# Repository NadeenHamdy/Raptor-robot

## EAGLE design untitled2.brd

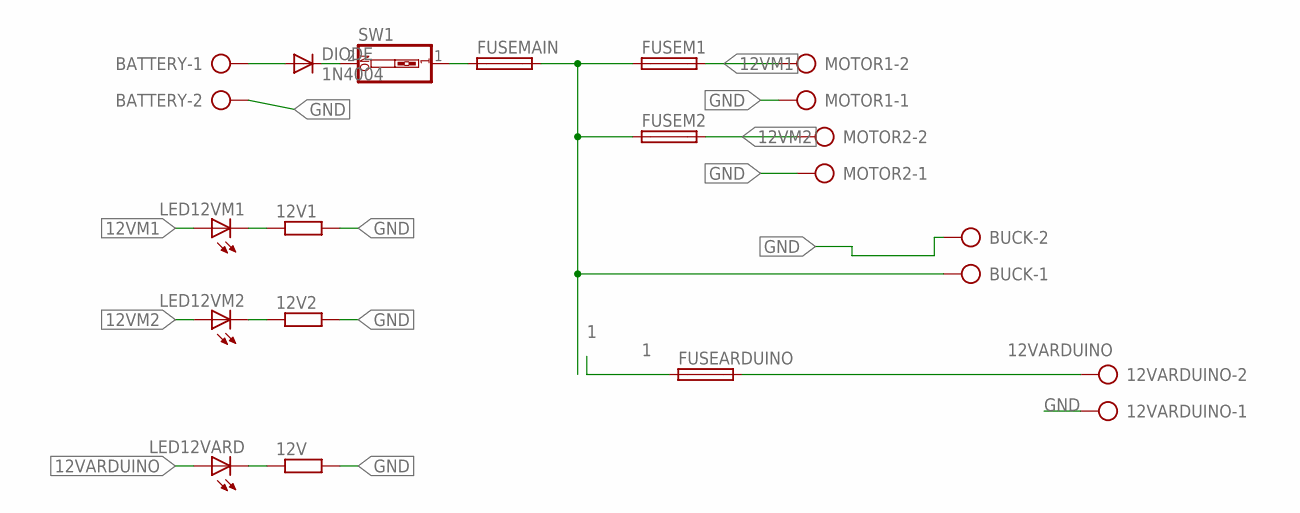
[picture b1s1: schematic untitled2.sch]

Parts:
12V, 12V1, 12V2: R-EU_0204/7; 0204/7
12VARDUINO: AK500/2-H
BATTERY: AK500/2-H
BUCK: AK500/2-H
DIODE: 1N4004; DO41-10
FUSEARDUINO: SH22,5
FUSEM1, FUSEM2: SH22,5
FUSEMAIN: SH22,5
LED12VARD, LED12VM1, LED12VM2: LEDLSU260; LSU260
MOTOR1, MOTOR2: AK500/2-H
SW1: SW_DIP-1; EDG-01

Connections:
1: BUCK.1, FUSEARDUINO.1, FUSEM1.1, FUSEM2.1, FUSEMAIN.2
12VARDUINO: 12VARDUINO.2, FUSEARDUINO.2, LED12VARD.A
12VM1: FUSEM1.2, LED12VM1.A, MOTOR1.2
12VM2: FUSEM2.2, LED12VM2.A, MOTOR2.2
GND: 12V.2, 12V1.2, 12V2.2, 12VARDUINO.1, BATTERY.2, BUCK.2, MOTOR1.1, MOTOR2.1
unnamed: BATTERY.1, DIODE.A
unnamed: DIODE.C, SW1.2
unnamed: FUSEMAIN.1, SW1.1
unnamed: 12V2.1, LED12VM2.K (C)
unnamed: 12V1.1, LED12VM1.K (C)
unnamed: 12V.1, LED12VARD.K (C)

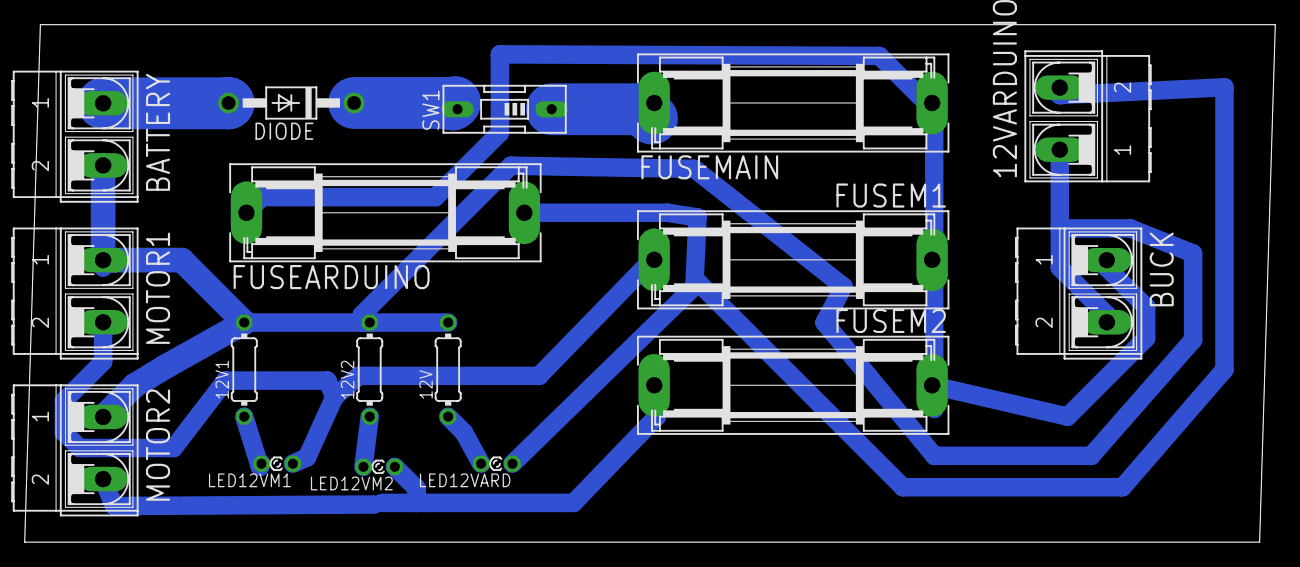
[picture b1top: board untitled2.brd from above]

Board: 2 copper layers, 101.3 x 41.9 mm, 17 parts (0 on the bottom side), 11 nets.

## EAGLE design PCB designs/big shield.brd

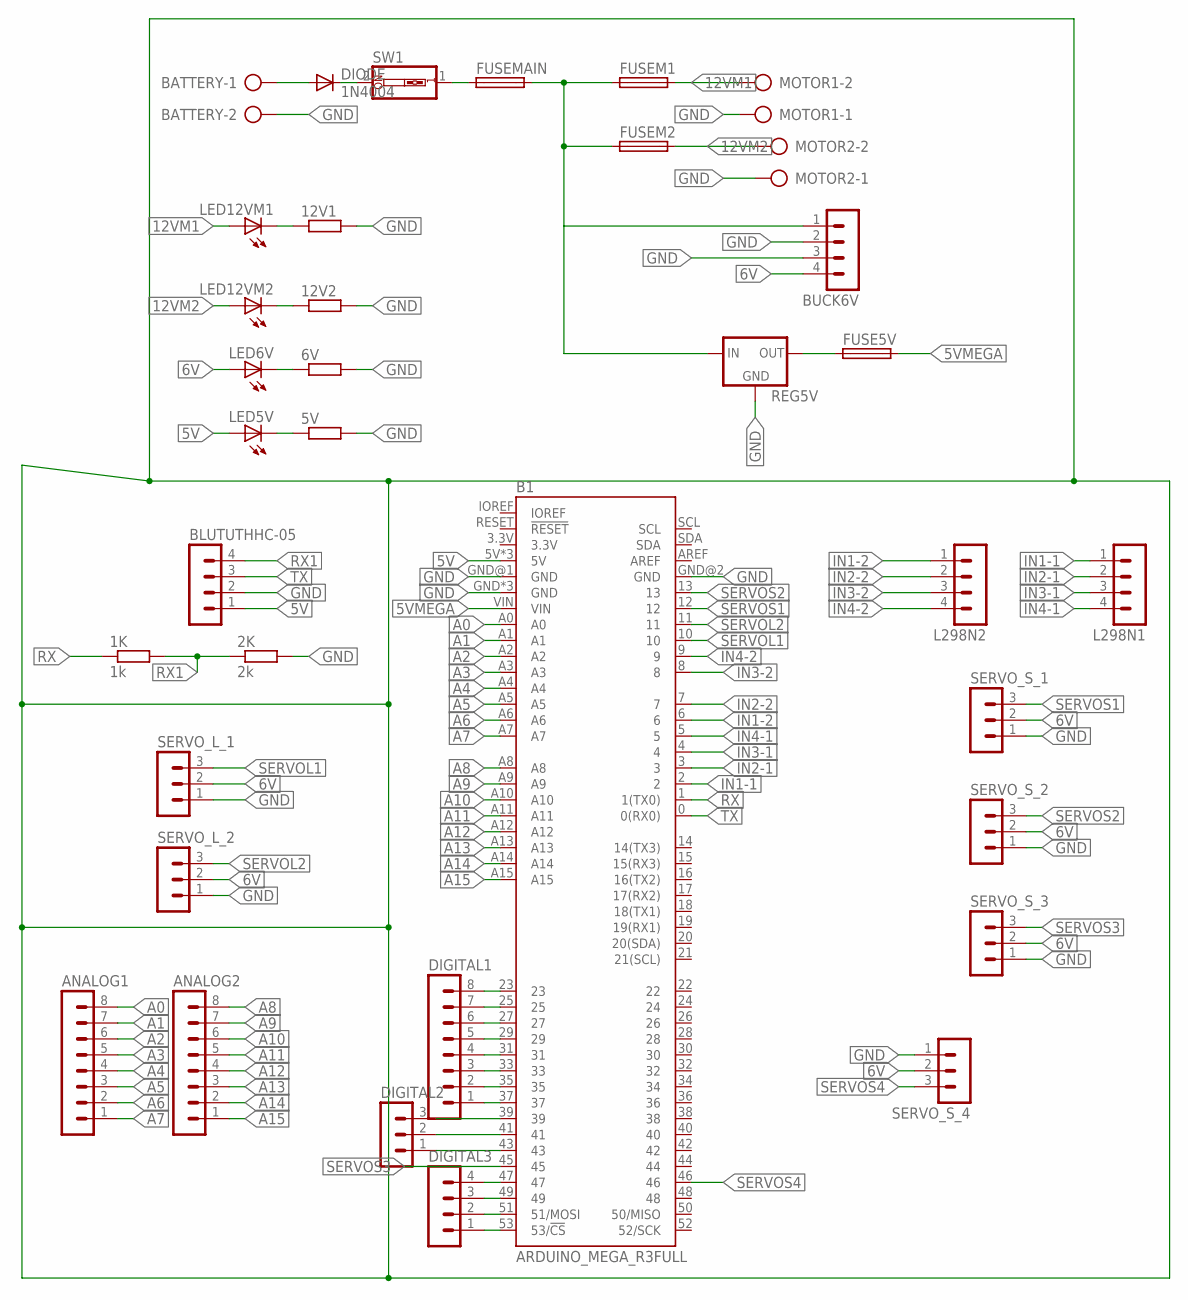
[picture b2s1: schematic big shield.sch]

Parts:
1K: 1k; 0207/10
2K: 2k; 0207/10
5V, 6V, 12V1, 12V2: R-EU_0204/7; 0204/7
ANALOG1, ANALOG2: MA08-1
B1: ARDUINO_MEGA_R3FULL; ARDUINO_MEGA_NO_SILK
BATTERY: AK500/2-H
BLUTUTHHC-05: MA04-1
BUCK6V: MA04-1
DIGITAL1: MA08-1
DIGITAL2: MA03-1
DIGITAL3: MA04-1
DIODE: 1N4004; DO41-10
FUSE5V: SH22,5
FUSEM1, FUSEM2: SH22,5
FUSEMAIN: SH22,5
L298N1, L298N2: MA04-1
LED5V, LED6V, LED12VM1, LED12VM2: LEDLSU260; LSU260
MOTOR1, MOTOR2: AK500/2-H
REG5V: 78XXS
SERVO_L_1, SERVO_L_2: MA03-1
SERVO_S_1, SERVO_S_2, SERVO_S_3, SERVO_S_4: MA03-1
SW1: SW_DIP-1; EDG-01

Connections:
5V: B1.5V, B1.5V@1 (5V), B1.5V@2 (5V), BLUTUTHHC-05.1, LED5V.A
5VMEGA: B1.VIN, FUSE5V.2
6V: BUCK6V.4, LED6V.A, SERVO_L_1.2, SERVO_L_2.2, SERVO_S_1.2, SERVO_S_2.2, SERVO_S_3.2, SERVO_S_4.2
12V1: BUCK6V.1, FUSEM1.1, FUSEM2.1, FUSEMAIN.2, REG5V.IN
12VM1: FUSEM1.2, LED12VM1.A, MOTOR1.2
12VM2: FUSEM2.2, LED12VM2.A, MOTOR2.2
A0: ANALOG1.8, B1.A0
A1: ANALOG1.7, B1.A1
A2: ANALOG1.6, B1.A2
A3: ANALOG1.5, B1.A3
A4: ANALOG1.4, B1.A4
A5: ANALOG1.3, B1.A5
A6: ANALOG1.2, B1.A6
A7: ANALOG1.1, B1.A7
A8: ANALOG2.8, B1.A8
A9: ANALOG2.7, B1.A9
A10: ANALOG2.6, B1.A10
A11: ANALOG2.5, B1.A11
A12: ANALOG2.4, B1.A12
A13: ANALOG2.3, B1.A13
A14: ANALOG2.2, B1.A14
A15: ANALOG2.1, B1.A15
GND: 2K.2, 5V.2, 6V.2, 12V1.2, 12V2.2, B1.GND, B1.GND@1 (GND), B1.GND@2 (GND), B1.GND@3 (GND), B1.GND@4 (GND), BATTERY.2, BLUTUTHHC-05.2, BUCK6V.2, BUCK6V.3, MOTOR1.1, MOTOR2.1, REG5V.GND, SERVO_L_1.1, SERVO_L_2.1, SERVO_S_1.1, SERVO_S_2.1, SERVO_S_3.1, SERVO_S_4.1
IN1-1: B1.2, L298N1.1
IN1-2: B1.6, L298N2.1
IN2-1: B1.3, L298N1.2
IN2-2: B1.7, L298N2.2
IN3-1: B1.4, L298N1.3
IN3-2: B1.8, L298N2.3
IN4-1: B1.5, L298N1.4
IN4-2: B1.9, L298N2.4
unnamed: BATTERY.1, DIODE.A
unnamed: DIODE.C, SW1.2
unnamed: FUSEMAIN.1, SW1.1
unnamed: FUSE5V.1, REG5V.OUT
unnamed: 6V.1, LED6V.K (C)
unnamed: 12V2.1, LED12VM2.K (C)
unnamed: 12V1.1, LED12VM1.K (C)
unnamed: 5V.1, LED5V.K (C)
unnamed: B1.23, DIGITAL1.8
unnamed: B1.25, DIGITAL1.7
unnamed: B1.27, DIGITAL1.6
unnamed: B1.29, DIGITAL1.5
unnamed: B1.31, DIGITAL1.4
unnamed: B1.33, DIGITAL1.3
unnamed: B1.35, DIGITAL1.2
unnamed: B1.37, DIGITAL1.1
unnamed: B1.39, DIGITAL2.3
unnamed: B1.41, DIGITAL2.2
unnamed: B1.43, DIGITAL2.1
unnamed: B1.47, DIGITAL3.4
unnamed: B1.49, DIGITAL3.3
unnamed: B1.51 (51/MOSI), DIGITAL3.2
unnamed: B1.53 (53/!CS), DIGITAL3.1
RX: 1K.1, B1.1 (1(TX0))
RX1: 1K.2, 2K.1, BLUTUTHHC-05.4
SERVOL1: B1.10, SERVO_L_1.3
SERVOL2: B1.11, SERVO_L_2.3
SERVOS1: B1.12, SERVO_S_1.3
SERVOS2: B1.13, SERVO_S_2.3
SERVOS3: B1.45, SERVO_S_3.3
SERVOS4: B1.46, SERVO_S_4.3
TX: B1.0 (0(RX0)), BLUTUTHHC-05.3

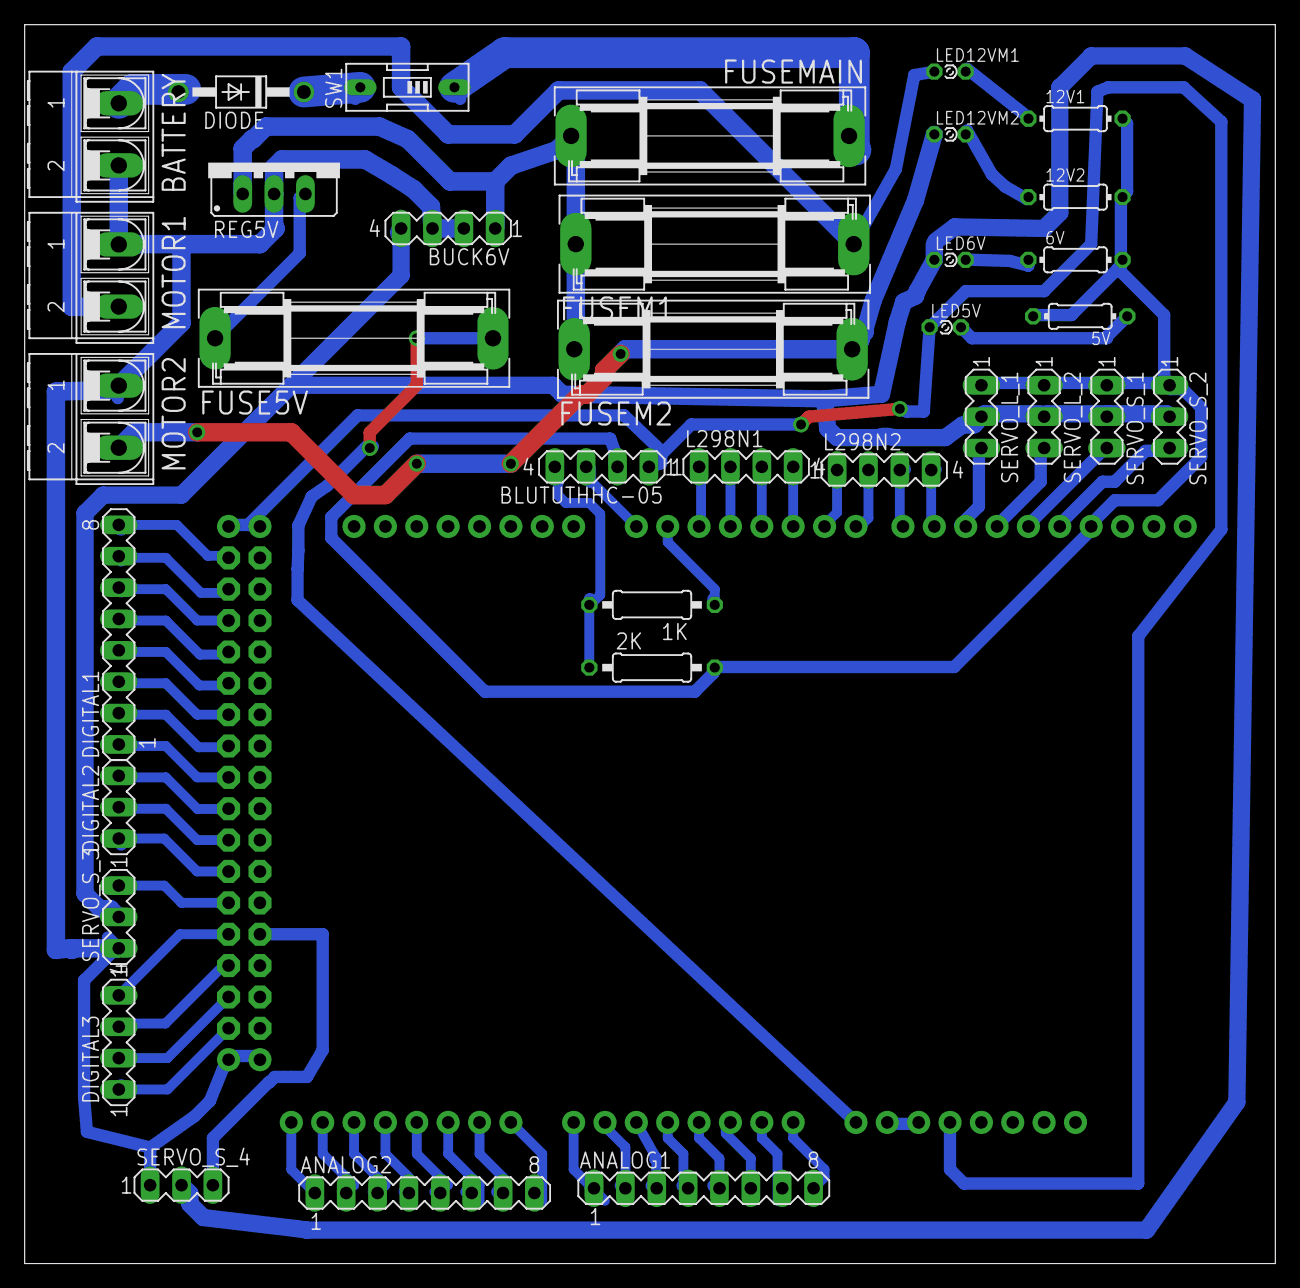
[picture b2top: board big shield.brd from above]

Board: 2 copper layers, 101.3 x 100.3 mm, 36 parts (1 on the bottom side), 63 nets.

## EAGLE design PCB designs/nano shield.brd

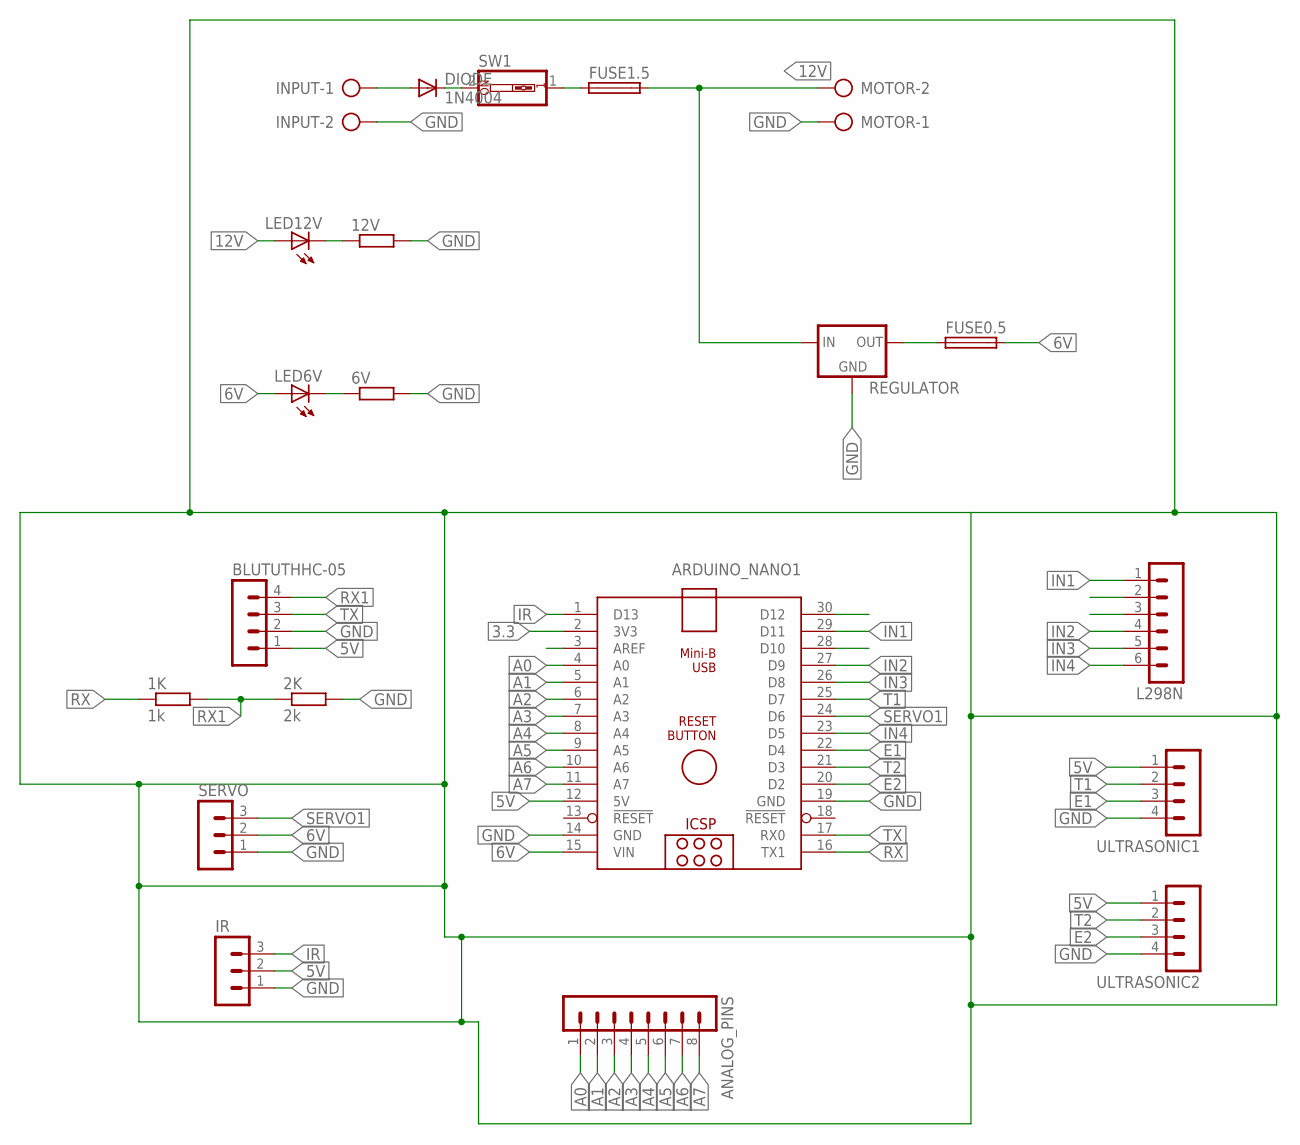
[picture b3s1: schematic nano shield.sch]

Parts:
1K: 1k; 0207/10
2K: 2k; 0207/10
6V, 12V: R-EU_0204/7; 0204/7
ANALOG_PINS: MA08-1
ARDUINO_NANO1: ARDUINO_NANO
BLUTUTHHC-05: MA04-1
DIODE: 1N4004; DO41-10
FUSE0.5, FUSE1.5: SH22,5
INPUT: AK500/2-H
IR: MA03-1
L298N: MA06-1
LED6V, LED12V: LEDLSU260; LSU260
MOTOR: AK500/2-H
REGULATOR: 78XXS
SERVO: MA03-1
SW1: SW_DIP-1; EDG-01
ULTRASONIC1, ULTRASONIC2: MA04-1

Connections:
3.3: ARDUINO_NANO1.2 (3V3)
5V: ARDUINO_NANO1.12 (5V), BLUTUTHHC-05.1, IR.2, ULTRASONIC1.1, ULTRASONIC2.1
6V: ARDUINO_NANO1.15 (VIN), FUSE0.5.2, LED6V.A, SERVO.2
12V: FUSE1.5.2, LED12V.A, MOTOR.2, REGULATOR.IN
A0: ANALOG_PINS.1, ARDUINO_NANO1.4 (A0)
A1: ANALOG_PINS.2, ARDUINO_NANO1.5 (A1)
A2: ANALOG_PINS.3, ARDUINO_NANO1.6 (A2)
A3: ANALOG_PINS.4, ARDUINO_NANO1.7 (A3)
A4: ANALOG_PINS.5, ARDUINO_NANO1.8 (A4)
A5: ANALOG_PINS.6, ARDUINO_NANO1.9 (A5)
A6: ANALOG_PINS.7, ARDUINO_NANO1.10 (A6)
A7: ANALOG_PINS.8, ARDUINO_NANO1.11 (A7)
E1: ARDUINO_NANO1.22 (D4), ULTRASONIC1.3
E2: ARDUINO_NANO1.20 (D2), ULTRASONIC2.3
GND: 2K.2, 6V.2, 12V.2, ARDUINO_NANO1.14 (GND), ARDUINO_NANO1.19 (GND), BLUTUTHHC-05.2, INPUT.2, IR.1, MOTOR.1, REGULATOR.GND, SERVO.1, ULTRASONIC1.4, ULTRASONIC2.4
IN1: ARDUINO_NANO1.30 (D12), L298N.1
IN2: ARDUINO_NANO1.27 (D9), L298N.4
IN3: ARDUINO_NANO1.26 (D8), L298N.5
IN4: ARDUINO_NANO1.23 (D5), L298N.6
IR: ARDUINO_NANO1.1 (D13), IR.3
unnamed: DIODE.A, INPUT.1
unnamed: DIODE.C, SW1.2
unnamed: FUSE1.5.1, SW1.1
unnamed: FUSE0.5.1, REGULATOR.OUT
unnamed: 6V.1, LED6V.K (C)
unnamed: 12V.1, LED12V.K (C)
PWM1: ARDUINO_NANO1.29 (D11), L298N.2
PWM2: ARDUINO_NANO1.28 (D10), L298N.3
RX: 1K.1, ARDUINO_NANO1.16 (TX1)
RX1: 1K.2, 2K.1, BLUTUTHHC-05.4
SERVO1: ARDUINO_NANO1.24 (D6), SERVO.3
T1: ARDUINO_NANO1.25 (D7), ULTRASONIC1.2
T2: ARDUINO_NANO1.21 (D3), ULTRASONIC2.2
TX: ARDUINO_NANO1.17 (RX0), BLUTUTHHC-05.3

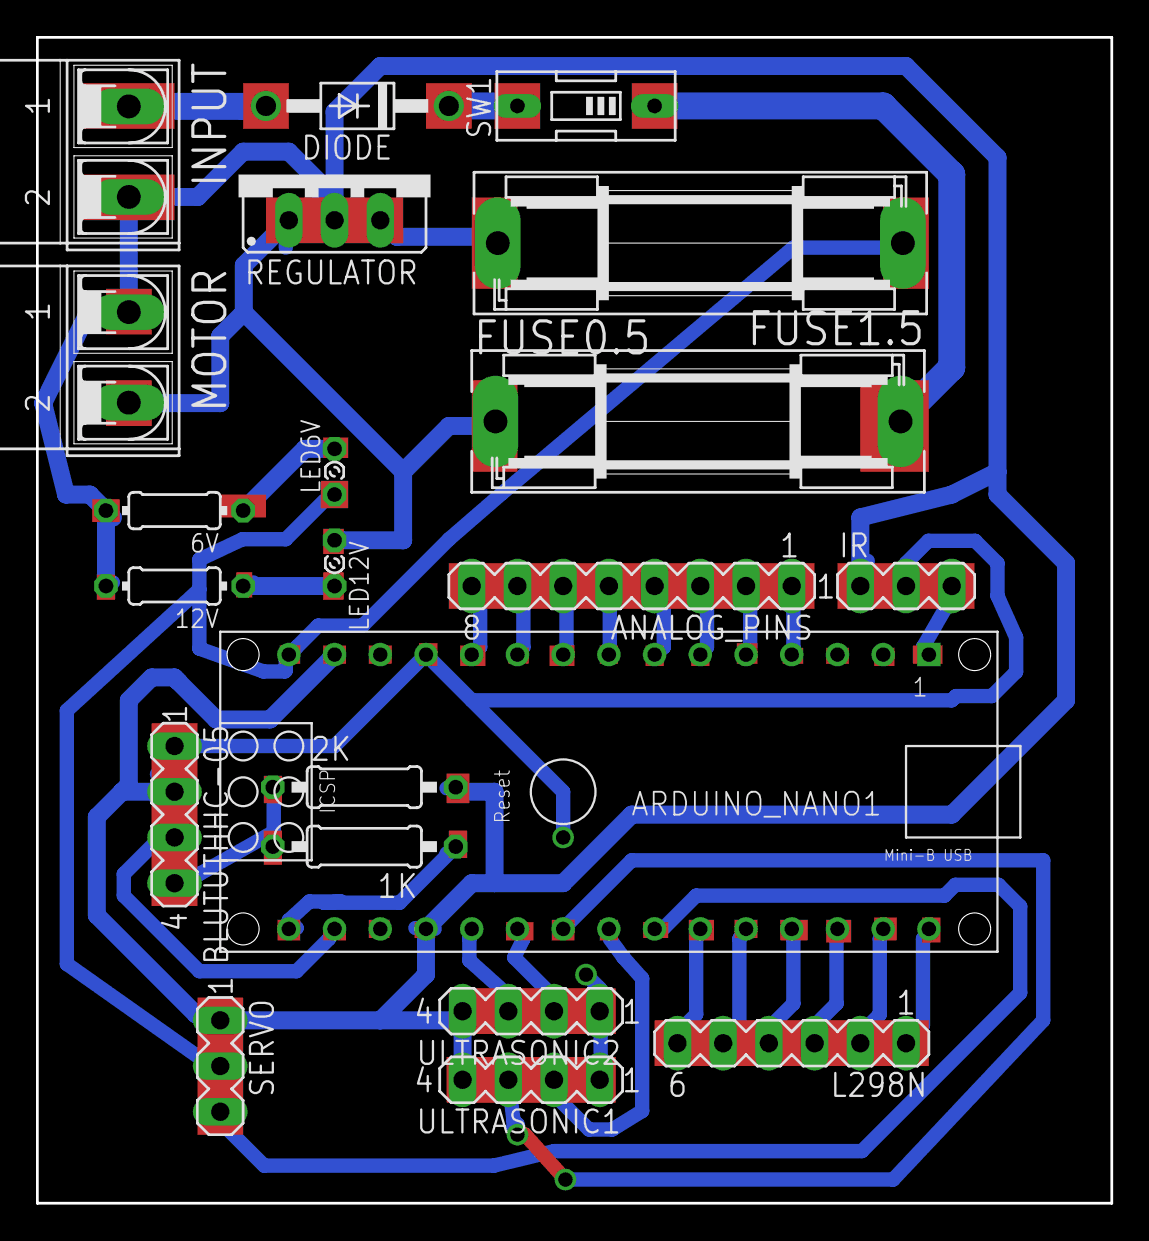
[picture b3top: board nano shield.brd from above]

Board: 2 copper layers, 59.7 x 64.8 mm, 21 parts (0 on the bottom side), 33 nets.

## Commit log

2021-08-30 robots

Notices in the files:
parts and their libraries:
SparkFun-Boards: Licensing: Creative Commons ShareAlike 4.0 International - https://creativecommons.org/licenses/by-sa/4.0
